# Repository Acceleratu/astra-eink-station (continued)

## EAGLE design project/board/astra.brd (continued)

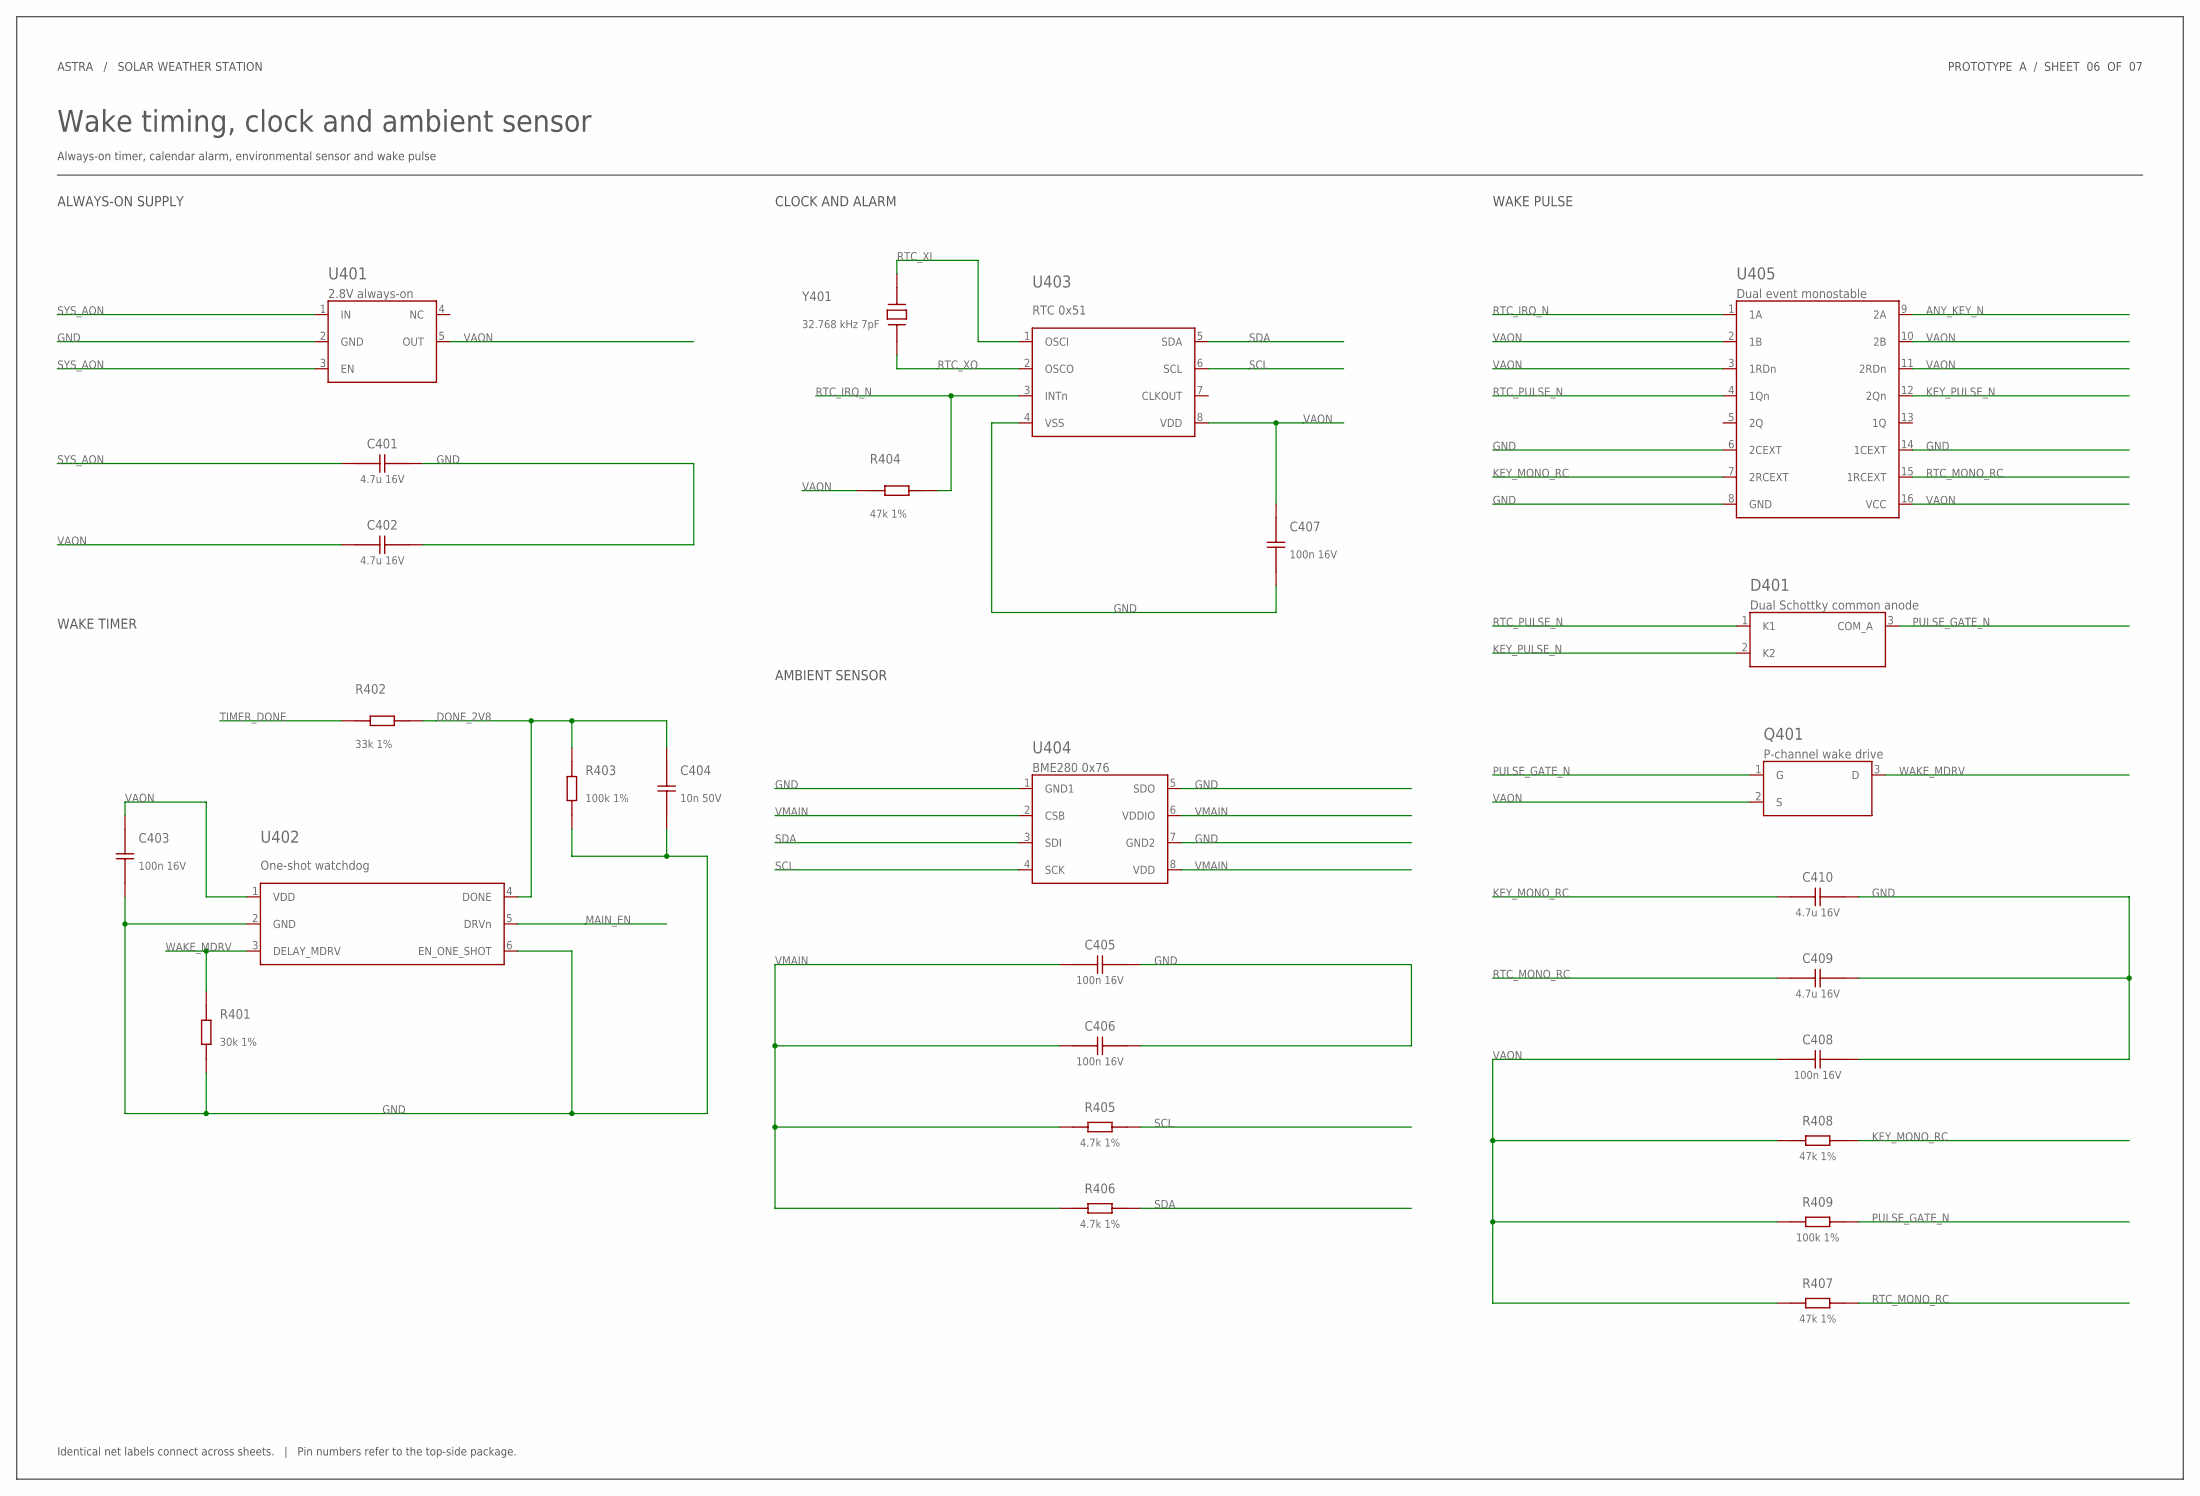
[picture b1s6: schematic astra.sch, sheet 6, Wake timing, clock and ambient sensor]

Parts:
C401, C402, C409, C410: 4.7u 16V; C0805; MPN CL21B475KOFNNNE; LCSC C107365
C403, C405, C406, C407, C408: 100n 16V; C0402; MPN CL05B104KO5NNNC; LCSC C1525
C404: 10n 50V; C0402; MPN CL05B103KB5NNNC; LCSC C15195
D401: Dual Schottky common anode; SOT23_WAKE; MPN BAT54A,215; LCSC C130910
Q401: P-channel wake drive; SOT23_WAKE; MPN AO3401A; LCSC C15127
R401: 30k 1%; R0402; MPN 0402WGF3002TCE; LCSC C25776
R402: 33k 1%; R0402; MPN 0402WGF3302TCE; LCSC C25779
R403, R409: 100k 1%; R0402; MPN 0402WGF1003TCE; LCSC C25741
R404, R407, R408: 47k 1%; R0402; MPN 0402WGF4702TCE; LCSC C25792
R405, R406: 4.7k 1%; R0402; MPN 0402WGF4701TCE; LCSC C25900
U401: 2.8V always-on; TI_DBV5_W; MPN TPS7A0228PDBVR; LCSC C5220176
U402: One-shot watchdog; TI_DDC6_TPL; MPN TPL5111DDCR; LCSC C2870554
U403: RTC 0x51; NXP_SO8_RTC; MPN PCF85063AT/AY; LCSC C5151540
U404: BME280 0x76; BOSCH_BME280; MPN BME280; LCSC C92489
U405: Dual event monostable; NXP_TSSOP16_MONO; MPN 74HC123PW,118; LCSC C426698
Y401: 32.768 kHz 7pF; ABRACON_ABS07; MPN ABS07-32.768KHZ-7-1-T; LCSC C1985277

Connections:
ANY_KEY_N: U405.9 (2A); also elsewhere on the board
DONE_2V8: C404.1, R402.2, R403.1, U402.4 (DONE)
GND: C401.2, C402.2, C403.2, C404.2, C405.2, C406.2, C407.2, C408.2, C409.2, C410.2, R401.2, R403.2, U401.2 (GND), U402.2 (GND), U402.6 (EN_ONE_SHOT), U403.4 (VSS), U404.1 (GND1), U404.5 (SDO), U404.7 (GND2), U405.6 (2CEXT), U405.8 (GND), U405.14 (1CEXT); also elsewhere on the board
KEY_MONO_RC: C410.1, R408.2, U405.7 (2RCEXT)
KEY_PULSE_N: D401.2 (K2), U405.12 (2Qn)
MAIN_EN: U402.5 (DRVn); also elsewhere on the board
PULSE_GATE_N: D401.3 (COM_A), Q401.1 (G), R409.2
RTC_IRQ_N: R404.2, U403.3 (INTn), U405.1 (1A)
RTC_MONO_RC: C409.1, R407.2, U405.15 (1RCEXT)
RTC_PULSE_N: D401.1 (K1), U405.4 (1Qn)
RTC_XI: U403.1 (OSCI), Y401.1 (XTAL1)
RTC_XO: U403.2 (OSCO), Y401.2 (XTAL2)
SCL: R405.2, U403.6 (SCL), U404.4 (SCK); also elsewhere on the board
SDA: R406.2, U403.5 (SDA), U404.3 (SDI); also elsewhere on the board
SYS_AON: C401.1, U401.1 (IN), U401.3 (EN); also elsewhere on the board
TIMER_DONE: R402.1; also elsewhere on the board
VAON: C402.1, C403.1, C407.1, C408.1, Q401.2 (S), R404.1, R407.1, R408.1, R409.1, U401.5 (OUT), U402.1 (VDD), U403.8 (VDD), U405.2 (1B), U405.3 (1RDn), U405.10 (2B), U405.11 (2RDn), U405.16 (VCC); also elsewhere on the board
VMAIN: C405.1, C406.1, R405.1, R406.1, U404.2 (CSB), U404.6 (VDDIO), U404.8 (VDD); also elsewhere on the board
WAKE_MDRV: Q401.3 (D), R401.1, U402.3 (DELAY_MDRV); also elsewhere on the board

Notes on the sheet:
ASTRA / SOLAR WEATHER STATION
Wake timing, clock and ambient sensor
Always-on timer, calendar alarm, environmental sensor and wake pulse
PROTOTYPE A / SHEET 06 OF 07
Identical net labels connect across sheets. | Pin numbers refer to the top-side package.
ALWAYS-ON SUPPLY
WAKE TIMER
CLOCK AND ALARM
AMBIENT SENSOR
WAKE PULSE

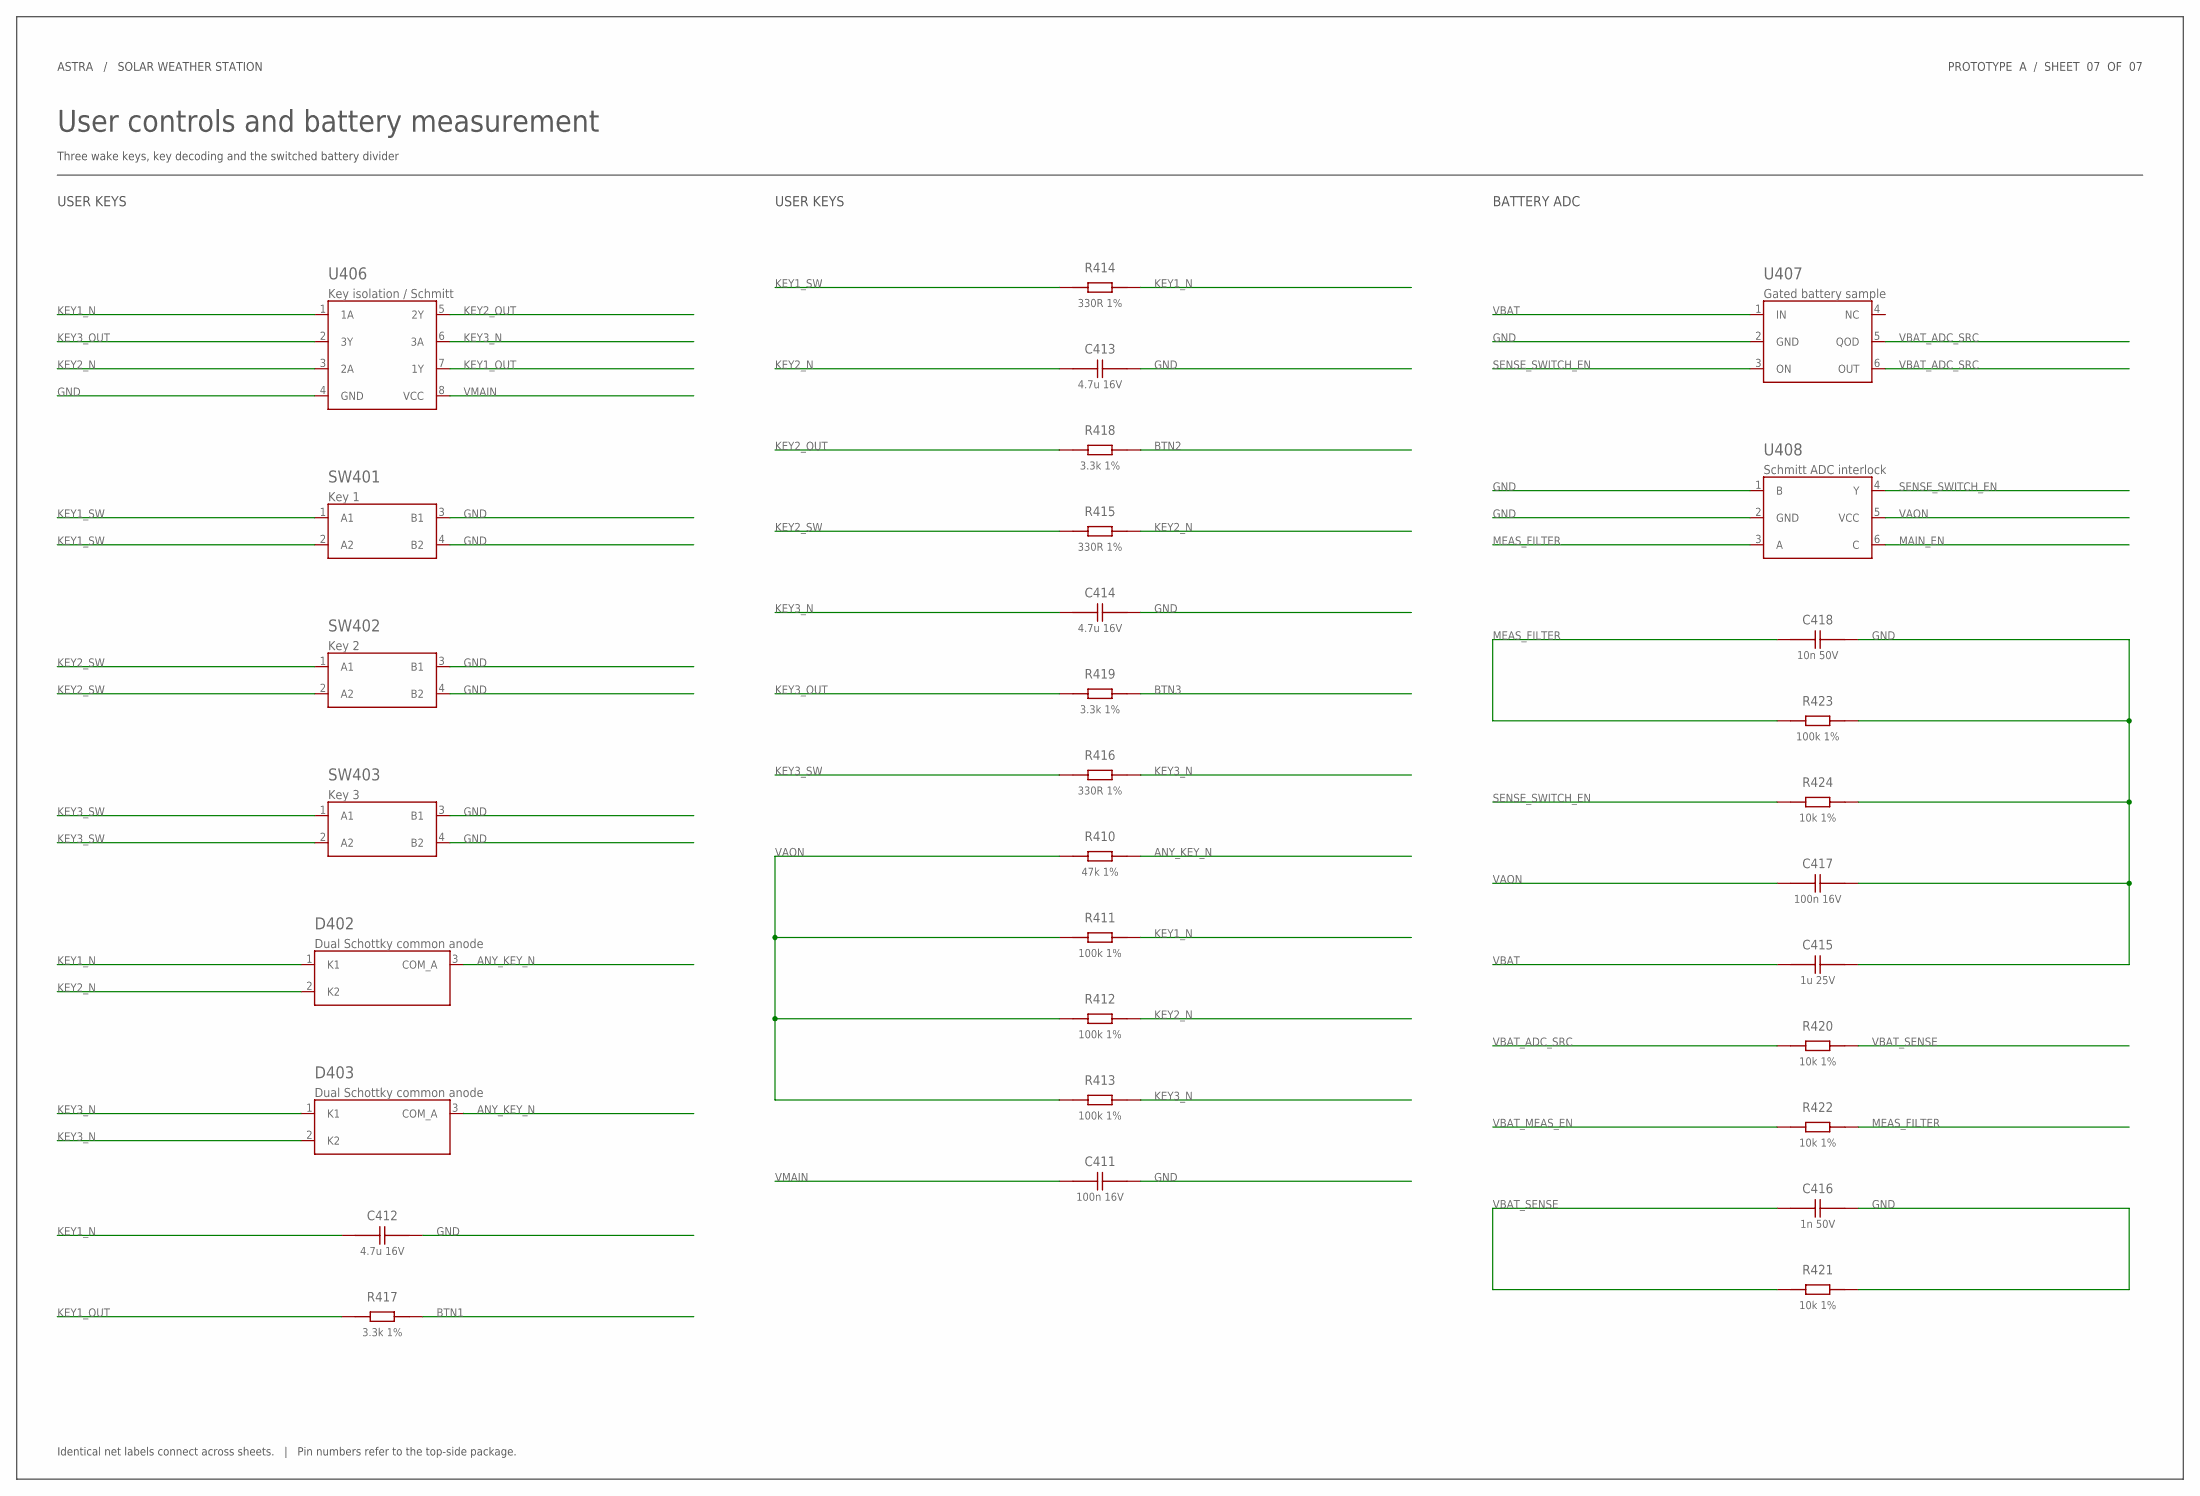
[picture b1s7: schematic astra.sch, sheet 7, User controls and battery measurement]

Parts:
C411, C417: 100n 16V; C0402; MPN CL05B104KO5NNNC; LCSC C1525
C412, C413, C414: 4.7u 16V; C0805; MPN CL21B475KOFNNNE; LCSC C107365
C415: 1u 25V; C0402; MPN CL05A105KA5NQNC; LCSC C52923
C416: 1n 50V; C0402; MPN 0402B102K500NT; LCSC C1523
C418: 10n 50V; C0402; MPN CL05B103KB5NNNC; LCSC C15195
D402, D403: Dual Schottky common anode; SOT23_WAKE; MPN BAT54A,215; LCSC C130910
R410: 47k 1%; R0402; MPN 0402WGF4702TCE; LCSC C25792
R411, R412, R413, R423: 100k 1%; R0402; MPN 0402WGF1003TCE; LCSC C25741
R414, R415, R416: 330R 1%; R0402; MPN 0402WGF3300TCE; LCSC C25104
R417, R418, R419: 3.3k 1%; R0402; MPN 0402WGF3301TCE; LCSC C25890
R420, R421, R422, R424: 10k 1%; R0402; MPN 0402WGF1002TCE; LCSC C25744
SW401: Key 1; ALPS_SKRP; MPN SKRPABE010; LCSC C115360
SW402: Key 2; ALPS_SKRP; MPN SKRPABE010; LCSC C115360
SW403: Key 3; ALPS_SKRP; MPN SKRPABE010; LCSC C115360
U406: Key isolation / Schmitt; TI_DCU8_KEY; MPN SN74AUP3G14DCUR; LCSC C2863927
U407: Gated battery sample; TI_DCK6_SENSE; MPN TPS22919DCKR; LCSC C2149796
U408: Schmitt ADC interlock; TI_DCK6_SENSE; MPN SN74AUP1G97DCKR; LCSC C2682139

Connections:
ANY_KEY_N: D402.3 (COM_A), D403.3 (COM_A), R410.2; also elsewhere on the board
BTN1: R417.2; also elsewhere on the board
BTN2: R418.2; also elsewhere on the board
BTN3: R419.2; also elsewhere on the board
GND: C411.2, C412.2, C413.2, C414.2, C415.2, C416.2, C417.2, C418.2, R421.2, R423.2, R424.2, SW401.3 (B1), SW401.4 (B2), SW402.3 (B1), SW402.4 (B2), SW403.3 (B1), SW403.4 (B2), U406.4 (GND), U407.2 (GND), U408.1 (B), U408.2 (GND); also elsewhere on the board
KEY1_N: C412.1, D402.1 (K1), R411.2, R414.2, U406.1 (1A)
KEY1_OUT: R417.1, U406.7 (1Y)
KEY1_SW: R414.1, SW401.1 (A1), SW401.2 (A2)
KEY2_N: C413.1, D402.2 (K2), R412.2, R415.2, U406.3 (2A)
KEY2_OUT: R418.1, U406.5 (2Y)
KEY2_SW: R415.1, SW402.1 (A1), SW402.2 (A2)
KEY3_N: C414.1, D403.1 (K1), D403.2 (K2), R413.2, R416.2, U406.6 (3A)
KEY3_OUT: R419.1, U406.2 (3Y)
KEY3_SW: R416.1, SW403.1 (A1), SW403.2 (A2)
MAIN_EN: U408.6 (C); also elsewhere on the board
MEAS_FILTER: C418.1, R422.2, R423.1, U408.3 (A)
SENSE_SWITCH_EN: R424.1, U407.3 (ON), U408.4 (Y)
VAON: C417.1, R410.1, R411.1, R412.1, R413.1, U408.5 (VCC); also elsewhere on the board
VBAT: C415.1, U407.1 (IN); also elsewhere on the board
VBAT_ADC_SRC: R420.1, U407.5 (QOD), U407.6 (OUT)
VBAT_MEAS_EN: R422.1; also elsewhere on the board
VBAT_SENSE: C416.1, R420.2, R421.1; also elsewhere on the board
VMAIN: C411.1, U406.8 (VCC); also elsewhere on the board

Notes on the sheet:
ASTRA / SOLAR WEATHER STATION
User controls and battery measurement
Three wake keys, key decoding and the switched battery divider
PROTOTYPE A / SHEET 07 OF 07
Identical net labels connect across sheets. | Pin numbers refer to the top-side package.
USER KEYS
BATTERY ADC

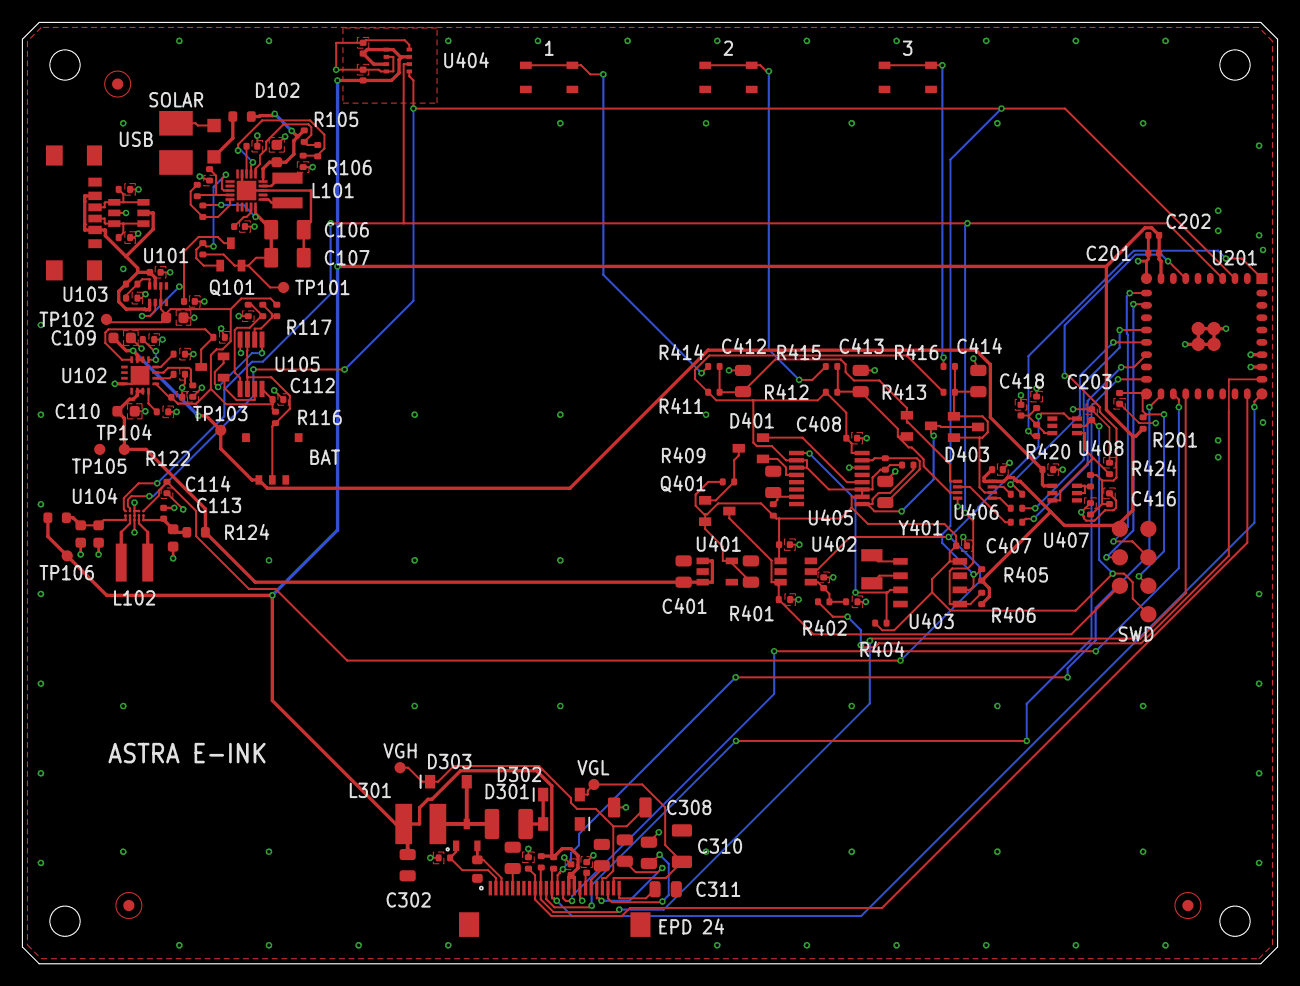
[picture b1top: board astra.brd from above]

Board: 2 copper layers, 112.0 x 84.0 mm, 149 parts (0 on the bottom side), 92 nets.

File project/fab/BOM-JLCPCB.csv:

Comment,Designator,Footprint,LCSC Part #,Manufacturer Part Number,Quantity per board
1n 50V,C416,C0402,C1523,0402B102K500NT,1
33 pF,C203,C0402,C1562,0402CG330J500NT,1
10 kΩ,R201,R0402,C25744,0402WGF1002TCE,1
10k 1%,"R112,R301,R420,R421,R422,R424",R0402,C25744,0402WGF1002TCE,6
100k 1%,"R104,R303,R304,R305,R403,R409,R411,R412,R413,R423",R0402,C25741,0402WGF1003TCE,10
1M 1%,"R111,R122",R0402,C26083,0402WGF1004TCE,2
1.5M 1%,"R107,R109",R0402,C22276,0402WGF1504TCE,2
2k 1%,R113,R0402,C4109,0402WGF2001TCE,1
22k 1%,"R116,R118,R119,R120",R0402,C25768,0402WGF2202TCE,4
2.7M 1%,R110,R0402,C270621,0402WGF2704TCE,1
30k 1%,R401,R0402,C25776,0402WGF3002TCE,1
301k 1%,R103,R0402,C25775,0402WGF3013TCE,1
330R 1%,"R414,R415,R416",R0402,C25104,0402WGF3300TCE,3
3.3k 1%,"R417,R418,R419",R0402,C25890,0402WGF3301TCE,3
33k 1%,R402,R0402,C25779,0402WGF3302TCE,1
360k 1%,R106,R0402,C45956,0402WGF3603TCE,1
4.7k 1%,"R123,R405,R406",R0402,C25900,0402WGF4701TCE,3
47k 1%,"R404,R407,R408,R410",R0402,C25792,0402WGF4702TCE,4
5.1k 1%,"R101,R102",R0402,C25905,0402WGF5101TCE,2
62k 1%,R117,R0402,C37825,0402WGF6202TCE,1
68k 1%,R114,R0402,C36871,0402WGF6802TCE,1
6.8M 1%,"R105,R108",R0402,C620473,0402WGF6804TCE,2
8.66k 1%,R115,R0402,C270576,0402WGF8661TCE,1
Dual event monostable,U405,NXP_TSSOP16_MONO,C426698,"74HC123PW,118",1
32.768 kHz 7pF,Y401,ABRACON_ABS07,C1985277,ABS07-32.768KHZ-7-1-T,1
AO3401A,Q101,SOT23_AO3401A,C15127,AO3401A,1
P-channel wake drive,Q401,SOT23_WAKE,C15127,AO3401A,1
Dual Schottky common anode,"D401,D402,D403",SOT23_WAKE,C130910,"BAT54A,215",3
"BAT54C,215",D103,NXP_SOT23_DIODE,C37704,"BAT54C,215",1
"LP223439 pack, black / yellow / red",J102,JST_ACH03P_POWER,C5118705,BM03B-ACHSS-GAN-ETF(LF)(SN),1
BME280 0x76,U404,BOSCH_BME280,C92489,BME280,1
BQ24074RGTR,U102,TI_RGT16_BQ74,C54313,BQ24074RGTR,1
BSS138L 50V NMOS,Q301,BSS138_CASE318,C82045,BSS138LT1G,1
1 µF,C202,C0402,C52923,CL05A105KA5NQNC,1
1u 25V,C415,C0402,C52923,CL05A105KA5NQNC,1
1uF 25V X5R,C305,C0402,C52923,CL05A105KA5NQNC,1
1uF 16V X5R,"C101,C105,C108,C111",C0402,C29266,CL05A105KO5NNNC,4
10nF 25V X7R,C104,C0402,C318576,CL05B103KA5NNNC,1
10n 50V,"C404,C418",C0402,C15195,CL05B103KB5NNNC,2
100 nF,C201,C0402,C1525,CL05B104KO5NNNC,1
100n 16V,"C403,C405,C406,C407,C408,C411,C417",C0402,C1525,CL05B104KO5NNNC,7
100nF 16V X7R,"C112,C114,C304",C0402,C1525,CL05B104KO5NNNC,3
4.7uF 25V X5R,C302,C0805,C1779,CL21A475KAQNNNE,1
1uF 50V X7R,"C303,C306,C307,C309,C311",C0805,C28323,CL21B105KBFNNNE,5
4.7u 16V,"C401,C402,C409,C410,C412,C413,C414",C0805,C107365,CL21B475KOFNNNE,7
1uF 100V X7R,"C308,C310",EPD_C1206,C13832,CL31B105KCHNNNE,2
4.7uF 50V X7R,C301,EPD_C1210,C47783,CL32B475KBJNNNE,1
nRF54L15-QFAA + 2.4 GHz PCB antenna,U201,EBYTE_08S1F_LGA40,C54337734,E73-2G4M08S1F,1
0R 1A DFT input,R124,R0603,C122704,ERJ3GEY0R00V,1
0R 1A DFT output,R125,R0603,C122704,ERJ3GEY0R00V,1
0R 1A DFT solar,R126,R0603,C122704,ERJ3GEY0R00V,1
EPD FPC 24 bottom-contact,J301,FH12_24S_05SH,C202112,FH12-24S-0.5SH(55),1
22uF 10V X5R,"C115,C116",C0603,C84419,GRM188R61A226ME15D,2
22uF 16V X5R,"C109,C110,C113",C0603,C5116073,GRM188R61C226ME01D,3
4.7uF 16V X5R,"C102,C103",C0603,C77045,GRM188R61C475KE11D,2
47uF 10V X5R,"C106,C107",C1206P,C426659,GRM31CR61A476KE15L,2
MBR0530 30V Schottky,"D301,D302,D303",MBR0530_CASE425,C82046,MBR0530T1G,3
MCP6542-I/MS,U105,MC_MSOP8_TEMP,C636338,MCP6542-I/MS,1
RTC 0x51,U403,NXP_SO8_RTC,C5151540,PCF85063AT/AY,1
"PMEG2010ER,115",D102,NXP_CFP3_DIODE,C82288,"PMEG2010ER,115",1
3R 1% 100mW,R302,R0603,C137724,RC0603FR-073RL,1
RT6160AWSC,U104,RT_WLCSP15,C7065276,RT6160AWSC,1
Key 1,SW401,ALPS_SKRP,C115360,SKRPABE010,1
Key 2,SW402,ALPS_SKRP,C115360,SKRPABE010,1
Key 3,SW403,ALPS_SKRP,C115360,SKRPABE010,1
Schmitt ADC interlock,U408,TI_DCK6_SENSE,C2682139,SN74AUP1G97DCKR,1
Key isolation / Schmitt,U406,TI_DCU8_KEY,C2863927,SN74AUP3G14DCUR,1
SPV1050TTR,U101,SPV_VFQFPN20,C5181469,SPV1050TTR,1
22uH 0.58A,L101,BOURNS_SRN3015,C2918094,SRN3015-220M,1
10uH 1.4A Isat,L301,SRN4018,C503307,SRN4018-100M,1
One-shot watchdog,U402,TI_DDC6_TPL,C2870554,TPL5111DDCR,1
TPS2116DRLR,U103,TI_DRL8_MUX,C3235557,TPS2116DRLR,1
Gated battery sample,U407,TI_DCK6_SENSE,C2149796,TPS22919DCKR,1
2.8V always-on,U401,TI_DBV5_W,C5220176,TPS7A0228PDBVR,1
USB-C power input,J101,GCT_USB4135,C5438410,USB4135-GF-A,1
USBLC6-2SC6,D101,ST_SOT23_6_ESD,C7519,USBLC6-2SC6,1
0.47uH 4.4A at 10% drop,L102,COIL_XGL4015,C5452431,XGL4015-471MEC,1

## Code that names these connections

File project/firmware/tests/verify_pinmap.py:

#!/usr/bin/env python3
"""Cross-check compiled, resolved Zephyr DT with Fusion XML library-to-pad mappings."""
import argparse
import csv
from hashlib import sha256
import os
from pathlib import Path
import sys
from xml.etree import ElementTree as ET

def main():
    ap = argparse.ArgumentParser(description=__doc__)
    ap.add_argument('--board', type=Path, help='also compare contactrefs in final Fusion board XML')
    ap.add_argument('--expect-board-sha256', help='require the exact released board SHA-256')
    ap.add_argument('--expect-schematic-sha256', help='require the exact released schematic SHA-256')
    ns = ap.parse_args()
    if ns.expect_board_sha256 and not ns.board:
        ap.error('--expect-board-sha256 requires --board')
    root = Path(__file__).resolve().parents[2]
    checked_files = [root/'schematic/astra.sch', root/'firmware/artifacts/resolved.dts',
                     root/'firmware/artifacts/astra.hex', root/'verification/radio/mcu-crosswalk.csv']
    if ns.board:
        checked_files.append(ns.board.resolve())
    def hashes():
        return {path:sha256(path.read_bytes()).hexdigest() for path in checked_files}
    original=hashes()
    if ns.expect_schematic_sha256:
        assert original[root/'schematic/astra.sch']==ns.expect_schematic_sha256, 'schematic SHA-256 mismatch'
    if ns.expect_board_sha256:
        assert original[ns.board.resolve()]==ns.expect_board_sha256, 'board SHA-256 mismatch'
    sys.path.insert(0, str(Path(os.environ['ZEPHYR_BASE']) / 'scripts/dts/python-devicetree/src'))
    from devicetree import dtlib
    dt = dtlib.DT(str(root / 'firmware/artifacts/resolved.dts'))
    user = dt.get_node('/zephyr,user')
    gpio = {}
    def pin(name,node,prop,index=0,want_active_low=False):
        cells = dtlib.to_nums(node.props[prop].value)
        phandle, bit, flags = cells[3*index:3*index+3]
        port = dt.phandle2node[phandle].props['port'].to_num()
        assert bool(flags & 1)==want_active_low
        gpio[name]=f'P{port}.{bit:02d}'
    pin('TIMER_DONE',user,'done-gpios')
    pin('VBAT_MEAS_EN',user,'measure-enable-gpios')
    for i in range(3):
        pin(f'BTN{i+1}',user,'button-gpios',i)
    pin('EPD_CS',dt.label2node['spi00'],'cs-gpios',want_active_low=True)
    pin('EPD_RST',user,'epd-reset-gpios',want_active_low=True)
    pin('EPD_BUSY',user,'epd-busy-gpios')
    pin('EPD_DC',user,'epd-dc-gpios')
    for peripheral,functions in [('spi00',{4:'EPD_SCK',5:'EPD_MOSI'}),('i2c21',{11:'SCL',12:'SDA'})]:
        state=dt.label2node[peripheral].props['pinctrl-0'].to_nodes()[0]
        for sel in state.nodes['group1'].props['psels'].to_nums():
            gpio[functions[sel>>24]]=f'P{(sel & 0x1ff)//32}.{(sel & 31):02d}'
    ch=dt.label2node['adc'].nodes['channel@0']
    # Zephyr v4.3.0 adc_nrfx_saadc.c explicitly maps nRF54L15 AIN0 (binding value 1) to P1.04.
    assert ch.props['zephyr,input-positive'].to_num()==1 and ch.props['zephyr,resolution'].to_num()==12
    gpio['VBAT_SENSE']='P1.04'
    assert dt.label2node['bme'].props['reg'].to_num()==0x76
    assert dt.label2node['external_rtc'].props['reg'].to_num()==0x51
    assert dt.label2node['panel'].props['spi-max-frequency'].to_num()==2_000_000
    assert dt.label2node['panel'].props['spi-cs-setup-delay-ns'].to_num()==1000
    assert dt.label2node['panel'].props['spi-cs-hold-delay-ns'].to_num()==1000
    assert dt.label2node['i2c21'].props['clock-frequency'].to_num()==100_000
    assert dt.label2node['hfxo'].props['load-capacitance-femtofarad'].to_num()==15000
    assert dt.label2node['lfxo'].props['load-capacitance-femtofarad'].to_num()==17000
    rows = list(csv.DictReader((root/'verification/radio/mcu-crosswalk.csv').open()))
    crosswalk={r['carrier net']:r for r in rows}
    assert set(gpio)=={n for n,r in crosswalk.items() if r['MCU pin function'].startswith('P')}
    source=ET.parse(root/'schematic/astra.sch').find('.//schematic')
    part=source.find("./parts/part[@name='U201']")
    lib=source.find(f"./libraries/library[@name='{part.get('library')}']")
    dev=lib.find(f"./devicesets/deviceset[@name='{part.get('deviceset')}']/devices/device[@name='{part.get('device')}']")
    pads={(c.get('gate'),c.get('pin')):c.get('pad') for c in dev.findall('connects/connect')}
    physical={}
    for net in source.findall('sheets/sheet/nets/net'):
        for ref in net.findall(".//pinref[@part='U201']"):
            physical.setdefault(net.get('name'),set()).add(pads[ref.get('gate'),ref.get('pin')])
    # Also verify the opposite ends of each digital interface through the Fusion library.
    def contacts(ref):
        part=source.find(f"./parts/part[@name='{ref}']")
        library=source.find(f"./libraries/library[@name='{part.get('library')}']")
        device=library.find(f"./devicesets/deviceset[@name='{part.get('deviceset')}']/devices/device[@name='{part.get('device')}']")
        land={ (c.get('gate'),c.get('pin')):c.get('pad') for c in device.findall('connects/connect') }
        return {land[p.get('gate'),p.get('pin')]:net.get('name')
                for net in source.findall('sheets/sheet/nets/net')
                for p in net.findall(f".//pinref[@part='{ref}']")}
    far_ends={
        'J301':{'8':'GND','9':'EPD_BUSY','10':'EPD_RST','11':'EPD_DC','12':'EPD_CS','13':'EPD_SCK','14':'EPD_MOSI','15':'VMAIN','16':'VMAIN'},
        'U403':{'1':'RTC_XI','2':'RTC_XO','3':'RTC_IRQ_N','4':'GND','5':'SDA','6':'SCL','8':'VAON'},
        'U404':{'1':'GND','2':'VMAIN','3':'SDA','4':'SCL','5':'GND','6':'VMAIN','7':'GND','8':'VMAIN'},
        'J201':{'1':'GND','2':'VMAIN','3':'SWCLK','4':'SWDIO','5':'NRST','6':'WAKE_MDRV','7':'VAON'},
    }
    for ref, expected in far_ends.items():
        actual=contacts(ref)
        for pad,net in expected.items(): assert actual.get(pad)==net,(ref,pad,net,actual.get(pad))
    board={}
    if ns.board:
        board_contacts = {ref:{} for ref in far_ends}
        for net in ET.parse(ns.board).findall('.//board/signals/signal'):
            board[net.get('name')]={ref.get('pad') for ref in net.findall("contactref[@element='U201']")}
            for c in net.findall('contactref'):
                ref, pad = c.get('element'), c.get('pad')
                if ref in far_ends and pad in far_ends[ref]:
                    assert pad not in board_contacts[ref], (ref,pad,'duplicate contactref')
                    board_contacts[ref][pad]=net.get('name')
        assert board_contacts==far_ends, 'opposite-end contactrefs absent or on different nets' 
    for net,func in sorted(gpio.items()):
        row=crosswalk[net]; pad=row['module pad']
        assert row['MCU pin function']==func,(net,func,row)
        assert physical[net]=={pad},(net,physical.get(net),pad)
        if ns.board: assert board[net]=={pad},(net,board.get(net),pad)
        print(f'{net:16} {func:6} U201.{pad:2}  QFN48.{row["QFN48 physical pin"]}')
    for net in ('SWCLK','SWDIO','NRST'):
        assert physical[net]=={crosswalk[net]['module pad']}
        if ns.board: assert board[net]==physical[net]
    print('PASS 14 firmware signals and 3 SWD/reset lands against supplier crosswalk and Fusion schematic')
    if ns.board: print(f'PASS all 17 against Fusion board contactrefs in {ns.board.name}')
    print(f'PASS {sum(len(pads) for pads in far_ends.values())} opposite-end lands on J301 display, U403 RTC, U404 sensor and J201 pogo fixture')
    print('PASS ADC AIN0, BME=0x76, RTC=0x51, I2C 100 kHz, SPI 2 MHz, 1 us CS setup/hold and HF/LF load settings')

    assert hashes()==original, 'inputs changed during the comparison'
    print('\nSHA-256 of unchanged inputs before and after verification')
    for path,digest in original.items():
        name=path.relative_to(root) if path.is_relative_to(root) else path
        print(f'{digest}  {name}')

if __name__=='__main__': main()
